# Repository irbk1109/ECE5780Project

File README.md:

# ECE5780Project
Authors:
  Isaac Kime, Sam Wimmer, Sean Koo, Subin Kim
  
Purpose:
  This embedded system is to achieve an automatic garage parking system that indicates if the car is parked or at the gate. The documentation folder above contains all pictures of schematics and wire diagrams. 

Functionality:
  1. The IR sensor detects if the car is parked or at the gate
  2. STM32 microcontroller takes IR sensor value as an ADC interrupt.
  3. Whenever the status changes, the OLED screen is updated to indicate its status.

  Note: The PCB has additional features for our senior project, but we can use the wiring in the documentation file for our 5780 project. 

Basic Setup Instructions:
  1. Insert sensors into the 3D parking garage and assemble the garage.
  2. Connect the black ground, red voltage (5 volts or 3.3 volts but 5 volts preferred), and white output wires of the sensors to the PCB.
  3. Connect the outputs of the PCB to PB4 and PB5 of the STM32 microcontroller. (PB5 is parking status and PB4 is gate status)
  4. Connect OLED to the STM32 using connecting Ground to Ground, Vcc to 3.3 volts, SDA to PB7, and SCL to PB6.
  5. Download the main.c file and supporting OLED library then build and flash it to the microcontroller.
  6. Run the program.
  7. The status of a car at the gate or in the stall will be shown on the OLED screen as well as by the LEDs from the PCB.

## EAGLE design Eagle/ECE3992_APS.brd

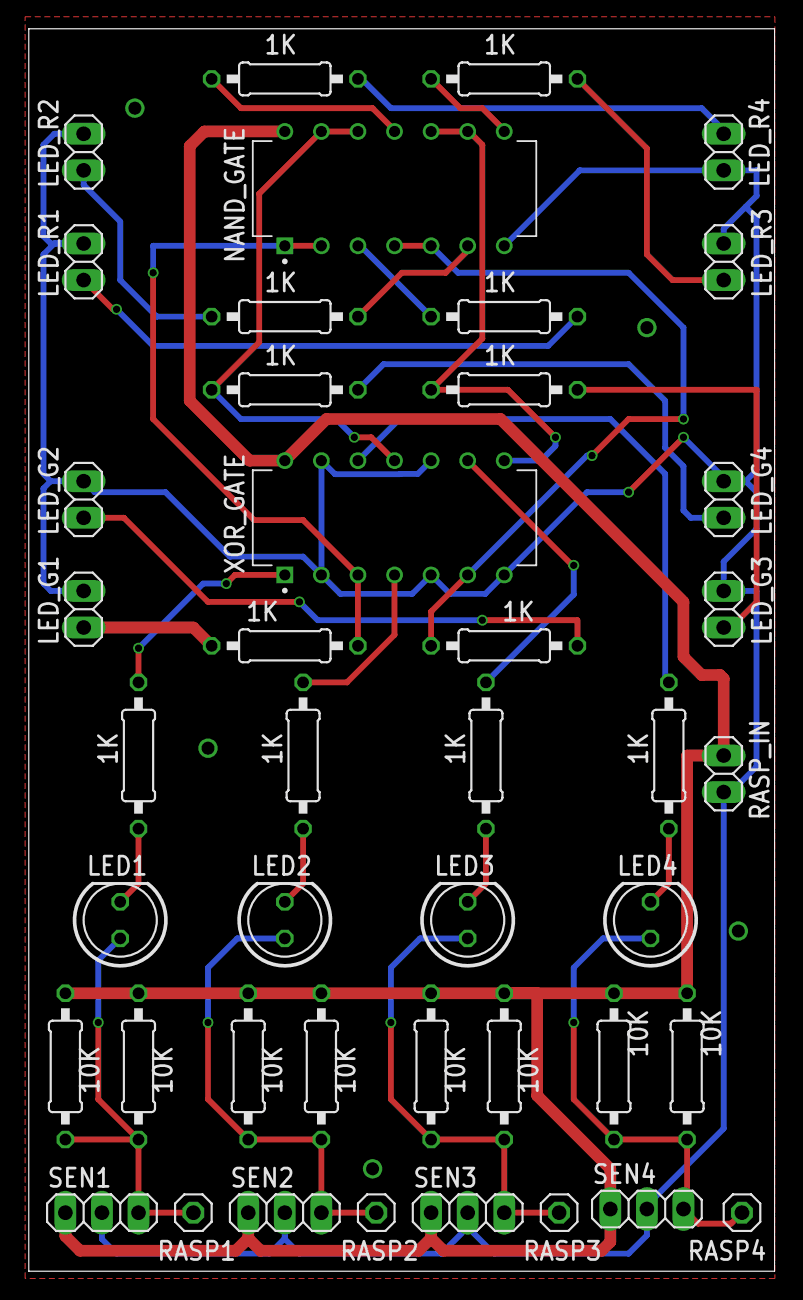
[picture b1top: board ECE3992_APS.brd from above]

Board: 2 copper layers, 51.8 x 86.3 mm, 43 parts (0 on the bottom side), 30 nets.

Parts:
1K: 1K; 0207/10
LED1, LED2, LED3, LED4: LED5MM
LED_G1, LED_G2, LED_G3, LED_G4: 1X02
LED_R1, LED_R2, LED_R3, LED_R4: 1X02
NAND_GATE: SN74HC00N; DIP794W45P254L1969H508Q14
R1, R11, R13, R15, R17, R18, R19, R20: 10K; 0207/10
R3, R4, R5, R6, R7, R8, R9, R10, R12, R14, R16: 1K; 0207/10
RASP1, RASP2, RASP3, RASP4: 1X01
RASP_IN: 1X02
SEN1, SEN2, SEN3, SEN4: 1X03
XOR_GATE: SN74HC86N; DIP794W45P254L1969H508Q14

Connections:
+3V3: NAND_GATE.14, R1.2, R11.2, R13.2, R15.2, R17.2, R18.2, R19.2, R20.2, RASP_IN.1, SEN1.1, SEN2.1, SEN3.1, SEN4.1, XOR_GATE.14
GND: LED_G1.2, LED_G2.2, LED_G3.2, LED_G4.2, LED_R1.2, LED_R2.2, LED_R3.2, LED_R4.2, NAND_GATE.7, RASP_IN.2, SEN1.2, SEN2.2, SEN3.2, SEN4.2, XOR_GATE.2, XOR_GATE.5, XOR_GATE.7, XOR_GATE.10, XOR_GATE.13
INV_1: NAND_GATE.1, NAND_GATE.2, R3.1, XOR_GATE.3
INV_2: NAND_GATE.4, NAND_GATE.5, R5.1, XOR_GATE.6
INV_3: NAND_GATE.9, NAND_GATE.10, R6.1, XOR_GATE.8
INV_4: NAND_GATE.12, NAND_GATE.13, R7.1, XOR_GATE.11
unnamed: LED1.A, R1.1, R11.1, RASP1.1, SEN1.3
unnamed: 1K.1, LED1.K
unnamed: LED_G1.1, R3.2
unnamed: LED_G2.1, R5.2
unnamed: LED_G3.1, R6.2
unnamed: LED_G4.1, R7.2
unnamed: LED_R1.1, R4.2
unnamed: LED_R2.1, R8.2
unnamed: LED_R3.1, R9.2
unnamed: LED_R4.1, R10.2
unnamed: NAND_GATE.6, R8.1
unnamed: NAND_GATE.3, R4.1
unnamed: LED2.K, R12.1
unnamed: LED2.A, R13.1, R15.1, RASP2.1, SEN2.3
unnamed: LED3.K, R14.1
unnamed: LED4.K, R16.1
unnamed: LED4.A, R19.1, R20.1, RASP4.1, SEN4.3
unnamed: LED3.A, R17.1, R18.1, RASP3.1, SEN3.3
unnamed: NAND_GATE.8, R9.1
unnamed: NAND_GATE.11, R10.1
SEN_1: 1K.2, XOR_GATE.1
SEN_2: R12.2, XOR_GATE.4
SEN_3: R14.2, XOR_GATE.9
SEN_4: R16.2, XOR_GATE.12

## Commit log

2024-03-19 Update README.md with Isaac's Name
2024-03-21 Updated by adding author Sam Wimmer to README.md
2024-03-22 Update README.md
    Adding my name Sean Koo
2024-03-22 Update README.md
    Added a name, Subin Kim
2024-03-28 Added comments in main.c to describe what the code needs to do
2024-03-31 Circuit Schematic upload
2024-03-31 Eagle/ECE3992_APS.sch
2024-03-31 Bottom sensors schematic upload
2024-03-31 Circuit Schematics upload
2024-03-31 upper PCB layout upload
2024-03-31 Upper PCB upload
2024-03-31 Upper PCB zip_file upload
2024-03-31 Update edited bottom PCB
2024-04-01 Bottom PCB layout Upload
2024-04-01 Shrunk the upper PCB and upload
2024-04-01 Upload edited PCB
2024-04-01 Upload edited version of PCB zip_file
2024-04-01 Upload bottom PCB zip_file
2024-04-02 Added lab code
    added lab code to try and start i2c for OLED
2024-04-03 Created Interupts for Timer and External
2024-04-03 added a write
2024-04-03 Pushing progress on OLED, not finished yet
2024-04-03 Created new layout for main file
    Made a new layout in order to verify if this solves our problem with the way we are sending data.
2024-04-03 added pin setup to main.c
    added pin setup for gate and parking.
2024-04-06 Find library and configured it to communicate with the OLED
2024-04-09 Initialized LEDs, Input GPIO, and check input
    Added an if statement to check if inputs are true and if they are then we change the LED status.
2024-04-09 Got reading the pin working
    We are reading pins PB4 and PB5
2024-04-18 Configured exti and syscfg for pb4
2024-04-18 Interfaced I2C OLED code with stm32
2024-04-18 Created OLED so parking status updates based on input read
2024-04-18 Finished Falling Edge interupt and timer
2024-04-18 Edit initial conditions to make start correct
2024-04-18 Finished Initial design for OLED screen
2024-04-18 Added Parking design
2024-04-24 Update README.md
    added basic setup instructions
2024-04-24 Update README.md
    updated basic setup instructions
2024-04-24 Update README.md
    Finish basic setup instructions
2024-04-24 Finalized Working Code
2024-04-24 Added Full example Project and Wiring Diagram
2024-04-24 Added top level block diagram
2024-04-25 Added the PCB Schematics and the board
